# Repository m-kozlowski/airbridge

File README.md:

# AirBridge

ESP32 bridge for ResMed AirSense 10 CPAP.

Using an AirSense 11? See [AirCANnect](https://github.com/m-kozlowski/aircannect).

## What it does

- **Web UI** - configure therapy settings, view sleep reports, live pressure/flow waveforms, and manage oximeters.
- **SD recording and export** - records therapy in Air10 EDF format and synchronizes files to SMB and SleepHQ on [SD-capable hardware](docs/hardware.md#what-needs-sd).
- **Oximetry** - feeds SpO2/pulse into AirSense for native SAD.edf recording. BLE (Nonin 3150, O2Ring, O2Ring-S, Checkme O2, WS20A, generic PLX/HR sensors) and UDP for integrating unsupported devices.
- **ResMed firmware** - upload and flash firmware over WiFi; keep images and save firmware dumps on SD-capable hardware.
- **TCP-UART bridge** - send commands to AirSense over WiFi.

## First setup

Follow the [Quick Start](docs/quickstart.md) to wire and flash your board.
On a fresh installation, connect to its `airbridge_...` WiFi network
(password `airbridge`), open `http://192.168.4.1/`, and complete the setup wizard.
Default Web UI login: `admin` / `airbridge`.

For HTTP integrations, see the [HTTP API reference](docs/http_api.md).

## Related tools

[airbreak-plus](https://github.com/m-kozlowski/airbreak-plus/tree/master/python/) contains Python tools for direct serial/TCP interaction:

- `python/resmed_flash.py -p tcp:airbridge` - flash AirSense firmware
- `python/resmed_config.py -p tcp:airbridge` - read/write AirSense settings

Both support serial (`-p /dev/ttyUSB0`) and TCP (`-p tcp:hostname`) with `--tcp-mode=raw|transparent|text`.

## Screenshots

| Dashboard | Edf Sync | Charts |
|---|---|---|
|  |  |  |

| Sleep Report | Clinical Settings | Oximetry |
|---|---|---|
|  |  |  |

## License

GPL v3. See [LICENSE](LICENSE).

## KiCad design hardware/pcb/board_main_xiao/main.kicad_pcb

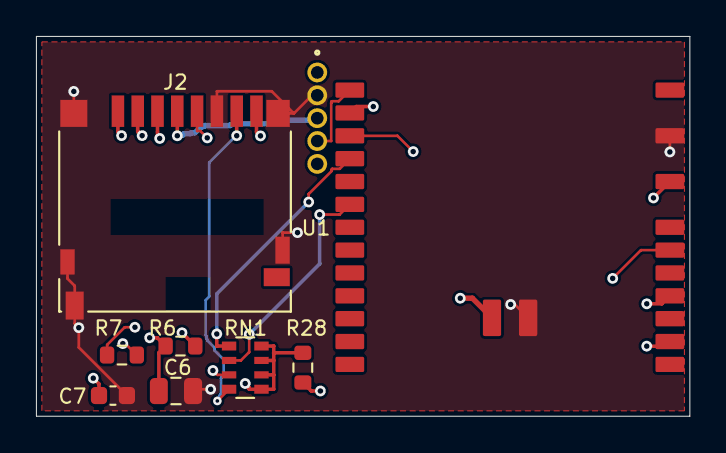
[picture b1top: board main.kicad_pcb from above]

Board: 4 copper layers, 36.3 x 21.1 mm, 9 parts (0 on the bottom side), 12 nets.

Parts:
C6: 10uF 25V X5R; C_0805_2012Metric
C7: 100nF 50V; C_0603_1608Metric
J2: microSD DM3D-SF; microSD_HC_Hirose_DM3D-SF
J5: 5 soldered pins / 1.27mm; SolderPins_1x05_P1.27mm
R6: 10k; R_0603_1608Metric
R7: 22R; R_0603_1608Metric
R28: 100k; R_0603_1608Metric
RN1: 4x10k isolated; R_Array_Convex_4x0603
U1: XIAO ESP32S3 Plus; XIAO_Plus_BAT_25P

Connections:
/+3V3: C6.1, C7.1, J2.4, J5.3, R6.1, R28.2, RN1.5, RN1.6, RN1.7, RN1.8, U1.12
/GND: C6.2, C7.2, J2.6, J2.10, J2.11, J5.2, U1.13, U1.33
/SD_CLK: J2.5, R7.2
/SD_CLK_MCU: R7.1, U1.23
/SD_CMD: J2.3, RN1.3, U1.21
/SD_D0: J2.7, RN1.4, U1.22
/SD_D1: J2.8, R6.2, U1.15
/SD_D2: J2.1, RN1.1, U1.16
/SD_D3: J2.2, RN1.2, U1.17
/SYS_5V: J5.1, U1.32
/UART_RX_MCU: J5.5, R28.1, U1.2
/UART_TX_MCU: J5.4, U1.1

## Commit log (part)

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2026-03-23 v1.0.0 import
2026-03-23 Add build timestamp to $STATUS and webui
2026-03-23 add "Cache-Control: no-store" header to /api responses
2026-03-23 BLE: Handle EALREADY and EDONE connect errors (err=2, err=13)
    Improve BLE connect reliability and WEB UI stallness
2026-03-23 make hostname configurable
2026-03-23 More BLE tweaks
    Clear oxi_device_addr when matching bond is deleted
    Skip unbonded Nonin from auto-connect-first-found
2026-03-23 Add README.md and some screenshots
2026-03-23 WEBUI: Remove duplicated console tab
2026-03-23 add LICENSE
2026-03-23 Hadrware description stub
2026-03-24 WEBUI: Improve status page
    SSE push merge into cached state; re-render directly, instead of polling.
    drop boring technical stats, add Product Name and Serial#
    Fix feeding status: only show "yes" when actually streaming
2026-03-25 WEBUI: Sleep Report tab
2026-03-25 WEBUI: Persist active tab across page refresh
2026-03-25 Bare minimum hardware diagram
2026-03-25 documentation cosmetics
2026-03-25 WEBUI: identify tabs by function instead of numeric index
2026-03-27 WEBUI: remove unused System section in Device tab
2026-03-27 OXI: send data as L-frames instead of two separate P S #VAR
2026-03-27 some debug logging
2026-03-27 Update power supply requirements in hardware documentation
2026-03-28 Revise hardware.md
2026-03-28 fix provision.py when running in SCons
2026-03-28 explicitly use pioarduino espressif32
2026-03-28 BREAKING: repartitioning + ota partition migrator (part #1)
    Repartition flash from v1 (1.4MB app + resmed OTA) to v2 (1.9MB app)
    migrate-ota platformio target can be used to rewrite partition table
    with new layout without the need of serial flashing.
    After migration, firmware waits for OTA of the target firmware.
    Migration status is displayed on AirSense LCD.
2026-03-28 Fix compilation warnings
2026-03-28 repartitioning part #2: use inactive ota partition for resmed OTA
2026-03-29 ResMed firmware safety checks: CRC, BID, bootloader patch detection
2026-03-29 adjust default uart timeout
2026-03-29 DOCS: add quickstart, configuration reference and repartitioning description
2026-03-29 migrate-ota: unconditionally send LCA 0000 before setting new LCD text
2026-03-29 drop hardcoded uart timeouts whenever possible. use uart_cmd_timeout_ms
2026-03-29 WEBUI: Move web UI to www/index.html, gzip at build time
2026-03-30 Move WiFi core features into own module, add NTP and timezone support
    Move wifi_setup() from tcp_bridge.cpp into wifi.cpp
    Add NTP sync after STA connection. Server priority: cfg > DHCP > pool.ntp.org
2026-03-30 BUILD: fix generate_web_ui.py to trigger even if no web_ui.cpp is being built
2026-03-30 WEBUI: add helper to set/detect TZ string
2026-03-30 OXI: send current time/date to Nonin 3150 on connection (if ntp synced)
2026-03-30 WEBUI: add esp32 time and resmed time to dashboard
2026-03-30 OTA: Trim oversized stack buffers
2026-03-30 Two way time sync: Fallback to AirSense time if ntp sync failed
    Set AirSense time on successful ntp sync
2026-03-30 OXI: display lcd message when starting to feed oximetry data
2026-03-30 FIX: airsense date/time parsing: strptime is not suitable
    ...and the buffers were too small
2026-03-30 Background STA reconnect when in AP fallback mode
2026-03-31 Fix NTP server selection - use esp_sntp API directly
    configTzTime() calls esp_sntp_setserverfromdhcp(0) which disables
    DHCP NTP servers. Use esp_sntp_* API directly instead
2026-03-31 WIFI: Add SmartConfig WiFi provisioning
    When STA connect fails or no SSID configured, try SmartConfig for 60s
    before falling back to AP mode.
2026-03-31 BLE: Clean up BLE connect: disconnect stale, retry on EDONE
    Handle EALREADY by waiting for pending connect to complete
    live BLE values on Bluetooth tab
2026-03-31 Add LCD message timeout, auto-clear in arbiter task
2026-03-31 Add 50ms delay after scan stop before connect
2026-04-01 CLI: add $TIME and $TIMESYNC commands
2026-04-01 LOG: drop useless CAT_DBG category
2026-04-01 BRIDGE: fix transparent mode baud switch detection
    and properly track transparent mode idle timeout
2026-04-01 Update screenshots
2026-04-01 Refactor oximetry: extract oxi_arbiter from ble_oxi
    Separate transport-independent logic into oxi_arbiter.
    Prepares for adding additional oximetry transport modules.
2026-04-01 OXI: Add UDP oximetry transport
    7-byte PLX-compatible packets: [0x55][0xAB][flags][spo2_lo][spo2_hi][hr_lo][hr_hi]
    Config: udp_oxi_port (default 8025, 0=disabled)
2026-04-02 WEBUI: add descriptions of configuration options in Device tab
2026-04-02 OXI: BLE user experience overhaul
    User-initiated connections retry more aggressively than the current auto-reconnect loop.
    Improved Web UI BLE tabreactivity - all driven by SSE instead of polling.
    Properly stop feeding on source disconnect
2026-04-02 code cleanup: remove dead code
2026-04-02 code cleanup: Unify response parsing: add qframe_response_value()
2026-04-02 code cleanup: extract crc16_ccitt into shared table-based implementation
2026-04-02 arbiter: log responses and timeouts
2026-04-02 logging: persist log levels in NVS
2026-04-02 code cleanup: deduplicate BDD baud parsing and negotiation
2026-04-02 code cleanup: deduplicate state name arrays into inline functions
2026-04-02 code cleanup: add json_foreach_kv() to replace key-value parse loops
2026-04-02 code cleanup: eliminate double-serialization of scan results and config dump
2026-04-02 arbiter: fix send_cmd semaphore race on caller timeout
2026-04-02 code cleanup: mark NimBLE UUID statics as const
2026-04-02 code cleanup: replace powf() with lookup table in parse_sfloat()
    eliminates FP library call on every BLE oximetry notification
2026-04-02 code cleanup: Integer-only SFLOAT parsing
2026-04-02 udp: fix UDP task stack and log buffer
2026-04-02 oxi: auto-start feed in arbiter
    Move oxi_auto_start logic from oxi_ble.cpp into arbiter feed() so it works for any transport
2026-04-02 Logging levels have been made sane
2026-04-03 WEBUI: Redesign web UI: sidebar navigation, card-based dashboard (part#1)
2026-04-03 WEBUI: Add WiFi RSSI and uptime to status endpoint and SSE push
2026-04-03 Add source_id to oxi arbiter, show in dashboard via SSE
2026-04-03 Add Motor Hours to device card, update when therapy starts or stops
2026-04-03 Add time sync API and wire up dashboard clock buttons
    extract push_time_to_resmed() and pull_time_from_resmed() from main.cpp
    Add force_ntp_sync() to WiFiSetup
2026-04-04 Update screenshots and readme
2026-04-04 CLI: add $RESETREASON command
2026-04-04 Stack usage adjustments
    Reduce stack buffers in upload verification to prevent panic
    Bump live_sampler_task stack from 4096 to 6144
2026-04-04 Stream CRC16 during upload instead of re-reading partition
2026-04-04 BLE: Restructure BLE connect: full sequence inside retry loop
    fix break/continue in encryption block targeted potetially killing BLE task permanently
    fix onDisconnect race with set_state() after subscribe
    fix encryption/subscribe failures now retry within the attempt budget
2026-04-04 BLE: fix thread safety: target_addr, scan_results, subscribe checks
    target_addr changed from to char[18] to eliminate heap race between web task
    mutex on scan_results[] to synchronize NimBLE callbacks and reader tasks
2026-04-04 BLE: Show Connected badge instead of Connect button for active device
2026-04-04 OTA: Add AirBridge self-OTA via web UI
2026-04-07 WEBUI: Add all tabs to mobile bottom nav, make scrollable
2026-04-08 Rename crc16 to crc, add crc8_ccitt for Viatom devices
2026-04-08 OXI: Separate disconnect from disable in BLE oximetry
    disconnect() drops connection but stays in DISCONNECTED state auto-reconnect continues
    disable() drops connection and sets DISABLED, stopping all scanning.
2026-04-08 OXI: Add Wellue/Viatom oximeter support, conditional encryption
    Set Viatom device time on connect when NTP is synced
    Disconnect Viatom after 15 consecutive invalid readings
2026-04-08 Allow clearing HTTP and OTA passwords via config UI
    Only post changed config values, track originals via data-orig
    Skip HTTP auth when user and password are both empty
2026-04-09 WEBUI: Skip HTTP auth when user and password are both empty
2026-04-14 OXI: Add known-devices list for non-bonding oximeters
    New config option oxi_require_known:
    auto-connect only to devices that are either NimBLE-bonded or in the
    known-devices list. Devices are added to known-devices after successful
    user-initiated connect.
2026-04-15 pio: allow input in platformio monitor
2026-04-15 WIFI: Multi-network WiFi with scan-sort-connect and hysteresis roaming
    Check RSSI every 60s, 3 consecutive readings below -73 dBm triggers roam
    scan. Switch if better known network exists with 8db hysterysis.
    Suspended during therapy/oxi-streaming/OTA.
2026-04-15 oxi: Remove volatile from scan_result_count, now mutex-protected
2026-04-16 WIFI: implement missing hysterysis logic
2026-04-16 uart_arbiter: Fix send_cmd ticket UAF on caller timeout
    Stack-allocated tickets in send_cmd could be dereferenced by the arbiter
    after the caller's wait timed out and its stack frame unwound.
    Heap-allocate blocking tickets. Serialize the handoff with a cleanup_mutex
2026-04-16 oxi: Harden parse_sfloat against OOB and overflow
2026-04-16 Copy scan results under mutex instead of exposing the array
    get_scan_results() returned a pointer to the internal scan_results[]
    but the list can be altered by scan initiated by another sources
2026-04-16 Defer BLE bond deletion to the BLE task
    previous implementation called called vTaskDelay(500) inside
    AsyncWebServer handler, blocking the async response.
2026-04-16 Split log categories: add CAT_WIFI, drop CAT_INIT
2026-04-16 OTA: Suspend BLE during OTA
2026-04-17 Defer BLE bond deletion to the BLE task - missing declarations
2026-04-17 OXI: Drive OxiArbiter::poll() from main loop
2026-04-17 Lift debug server and web UI startup out of TcpBridge::task
2026-04-17 remove dead code
2026-04-17 oxi/ble: Guard scan start against concurrent scan_requested hits
2026-04-23 Fix serial provisioning: wrong command syntax + log interleaving
2026-04-25 Mention pin definitions in hardware.md
2026-04-29 WEBUI: respect safe-area-inset on mobile bottom nav
    fixes "save" button being half-covered by the gesture bar
2026-04-29 OXI: Chunk Viatom SetTIME writes to fix O2Ring disconnects
2026-05-01 WEBUI: respect safe-area-inset on mobile bottom nav - proper fix
